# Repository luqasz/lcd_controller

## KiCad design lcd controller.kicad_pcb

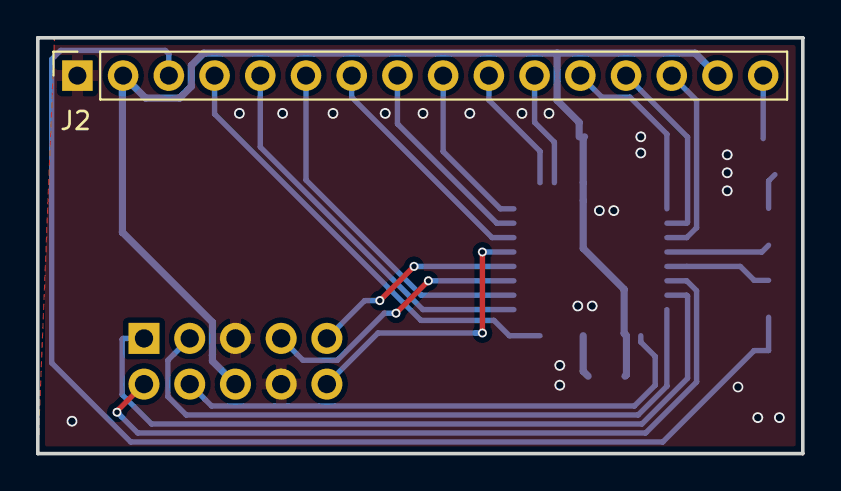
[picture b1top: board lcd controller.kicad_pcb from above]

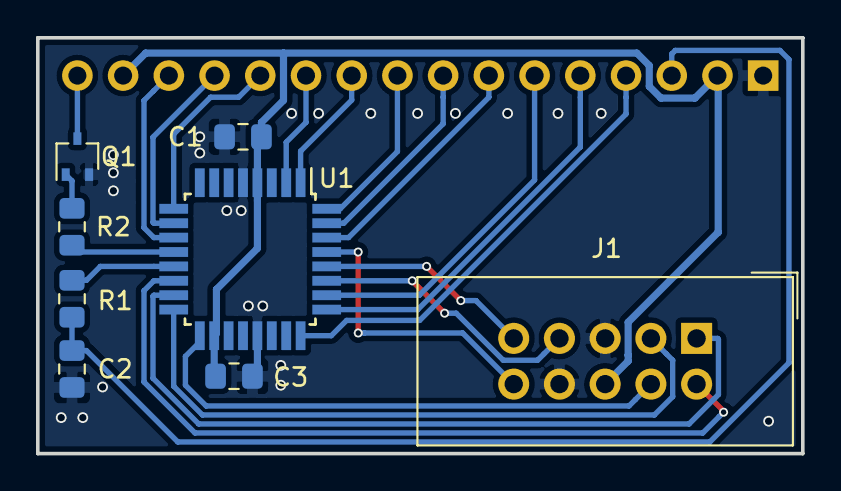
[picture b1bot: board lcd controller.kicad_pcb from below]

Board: 2 copper layers, 42.5 x 23.1 mm, 9 parts (8 on the bottom side), 25 nets.

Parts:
C1, C2, C3: 100n; C_0805_2012Metric_Pad1.15x1.40mm_HandSolder
J1: DATA; IDC-Header_2x05_P2.54mm_Vertical
J2: DISPLAY; PinSocket_1x16_P2.54mm_Vertical
Q1: BC817W; SOT-323_SC-70
R1: 100; R_0805_2012Metric_Pad1.15x1.40mm_HandSolder
R2: 2.2k; R_0805_2012Metric_Pad1.15x1.40mm_HandSolder
U1: ATmega328PB-AU; TQFP-32_7x7mm_P0.8mm

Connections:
/BACKLIGHT: R2.2, U1.12
/CON: C2.2, J2.3, R1.1
/D0: J2.7, U1.30
/D1: J2.8, U1.31
/D2: J2.9, U1.32
/D3: J2.10, U1.1
/D4: J2.11, U1.2
/D5: J2.12, U1.9
/D6: J2.13, U1.10
/D7: J2.14, U1.11
/E: J2.6, U1.26
/MISO: J1.3, U1.16
/MOSI: J1.1, U1.15
/RESET: J1.10, U1.29
/RS: J2.4, U1.24
/RW: J2.5, U1.25
/SCK: J1.4, U1.17
/SCL: J1.9, U1.28
/SDA: J1.7, U1.27
/SS: J1.2, U1.14
GND: C1.2, C2.1, C3.2, J1.5, J1.8, J2.1, Q1.2, U1.5, U1.21
unnamed: J2.16, Q1.3
unnamed: Q1.1, R2.1
unnamed: R1.2, U1.13
VCC: C1.1, C3.1, J1.6, J2.2, J2.15, U1.4, U1.18

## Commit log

2019-10-14 Update vias to their net class specs
2019-10-14 Ignore autosaves
2019-10-15 Shrink board
2019-10-15 Shrunk board
2019-10-15 Drag VCC line
2019-10-15 Drag SCK away from C3
